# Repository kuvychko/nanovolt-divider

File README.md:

# nanovolt-divider

A programmable precision attenuator for nanovolt-to-microvolt experiments: it divides an ordinary
bench power supply down by **passive resistive division**, read by an external precision DMM. Three
ratios (1e-5, 1e-6, 1e-7), relay-controlled polarity reversal for ABBA modulation, and a
source-disconnected baseline that opens the source without touching the measurement path.
Measured end to end down to 1.4 nV (see [Status](#status)).

| | |
|---|---|
|  |  |
| INJECTING: K5 set, the source drives the 1E-6 divider | ISOLATED: the source is open at both ends, the 1 Ω and OUT jacks stay connected |

| | |
|---|---|
| Ranges | `1E-5`, `1E-6`, `1E-7`: high legs of 100 kΩ (0.1 %, 5 ppm/°C), 1 MΩ (0.1 %, 10 ppm/°C) and 10 MΩ (1 %) over one shared 1 Ω low leg |
| Polarity | K4 reverses the source *upstream* of the high leg, so relay-contact EMFs reach the output divided by ~1/k |
| Baseline | ISOLATE opens the source at both ends; the 1 Ω, its Kelvin taps and the DMM path are never switched |
| Switching | Five latching relays, pulsed for 20 ms and never held: no continuous coil power |
| Temperature | TMP275 on a slotted island next to the 1 Ω: monitoring, and a check that the instrument is used inside its calibrated span |
| Calibration | A calibrated ratio k0 per range with its uncertainty and validated temperature span, stored in NVS and backed up to microSD. The firmware also supports a temperature correction k(T) = k0 [1 + α(T−T0) + β(T−T0)²]; this unit's records carry none ([why](docs/calibration.md#temperature-monitored-not-corrected)) |
| Control | SCPI over USB serial, and a 2.8" touchscreen (ESP32 "Cheap Yellow Display") |

## Status

Rev A is built and verified: all relay transitions work, and with 10 V applied all three ratios read
within 0.25 % of nominal, with the ISOLATE reading unchanged by the source. Firmware is 0.2.2.

**Calibration: complete.** The three ratios are measured (1E-5 to ±37 ppm over 21–27 °C, plus the DMM's
range-to-range accuracy), and an end-to-end test recovered every injected signal from 1 µV down to
**1.39 ± 0.24 nV** at its predicted level, with the switching null at −0.03 ± 0.24 nV. The records
were written to the instrument on 2026-10-16 and read back identical. The method, every result and
the stored records are in [docs/calibration.md](docs/calibration.md).

## Documentation

| Document | Contents |
|---|---|
| [docs/nanovolt_divider_rev_a.md](docs/nanovolt_divider_rev_a.md) | Design: architecture, relay rules, control, calibration model, BOM |
| [docs/hardware.md](docs/hardware.md) | Circuit, relay states, display harness wiring, board layout and routing rules |
| [docs/development.md](docs/development.md) | Opening the KiCad project, the ERC/DRC baseline, the generators and router, fabrication files |
| [docs/host_interface.md](docs/host_interface.md) | Driving it from a computer: the USB link, the reset-on-open trap, the SCPI contract |
| [docs/calibration.md](docs/calibration.md) | How the ratios are calibrated, the uncertainty budget, and the results so far |
| [firmware/README.md](firmware/README.md) | Building and flashing, the full SCPI command reference, first power-on |

## Repository layout

```
docs/                      design, hardware, development, host interface, calibration
calibration/               calibration result data (summaries and figures)
enclosure/                 SOLIDWORKS parts (.SLDPRT), STEP, and 3D-print files (.3MF, .3DXML)
firmware/                  ESP32 firmware, PlatformIO: relay state machine, SCPI over USB, touch UI,
                           microSD calibration backup and run log
hardware/                  KiCad 10 project
  nanovolt-divider.kicad_pro
  nanovolt-divider.kicad_sch   root sheet: metrology topology (input, relays, high legs, 1 ohm, output)
  control.kicad_sch            ESP32 display-module harness, MCP23017, TMP275, power
  relay_channel.kicad_sch      generic latching-relay channel, instantiated 5x (K1..K5)
  nanovolt-divider.kicad_pcb   board: 60 x 69.1 mm, 2 layers
  nanovolt-divider.kicad_dru   custom DRC rules (1 ohm bridge track width)
  lib/                         project symbol and footprint libraries
  fab/                         Rev A Gerbers and drill files
tools/gen_schematics.py    generates the schematics and the project libraries
tools/gen_pcb.py           generates the placed, unrouted board
tools/route_pcb.py         grid maze router around the hand routes (see docs/hardware.md)
tools/route_hand.py        the hand routes and routing policy: the design intent of the routing
tools/pcb_io.py            pcbnew side of the router: dump pads, apply routes
tools/scpi.py              SCPI terminal for the instrument over USB serial (uv run tools/scpi.py)
```

## Building one

1. **Boards.** Zip the contents of `hardware/fab/` and order (they went to OSH Park). Everything is
   hand-solderable; the BOM is in [§11 of the design doc](docs/nanovolt_divider_rev_a.md#11-bom).
2. **Harness.** Wire the display module to `J7` / `J8` **by signal name, never by pad number**: the
   board silk does not match the module. The table is in
   [docs/hardware.md, Display harness](docs/hardware.md#display-harness).
3. **Enclosure.** Print and assemble it as below.
4. **Firmware.** Build, flash and power on following [firmware/README.md](firmware/README.md).

## Enclosure

The enclosure is 3D-printed. `enclosure/` has the SOLIDWORKS source (`.SLDPRT`), a neutral `.STEP`
and a print-ready `.3MF` for each part: front panel (it also serves as the display bezel), back
panel, base plate (v1), cover (v1), PCB holder, and a wrench for the banana-jack nuts. The version
is in each file name.

Every part prints in PLA on a Prusa i3 MK3S with a 0.4 mm nozzle, using PrusaSlicer's
**0.20 mm QUALITY** preset, 15 % infill, and **no supports**.

Before assembling, heat-set the knurled brass inserts: the M2 ones go into the PCB holder, the M3
ones into the enclosure parts. Fasteners, banana jacks, the display module, and the cables are
listed in [BOM §11.4 and §11.5](docs/nanovolt_divider_rev_a.md#114-front-panel--mechanical).

| | |
|---|---|
|  |  |
| Cover off: the board on its holder, the display behind the front panel, and the jacks wired to their pads | Base plate with printed feet, and the back panel with the USB opening |

## Known limitations

* The board's harness silk and F.Fab text describe a different module pinout from the module the
  instrument uses. Wire by signal name (see
  [Display harness](docs/hardware.md#display-harness)).
* The harness cable has no strain relief at the board end; nothing on the board takes that load.

## Datasheets

Not redistributed here. Panasonic TQ relays: catalog ASCTB14E (`industry.panasonic.com`); Ohmite
MOX-700 and Slim-Mox; Vishay Dale RS/NS; Microchip MCP23017; TI TMP275.

## License

* Hardware (`hardware/`), enclosure (`enclosure/`) and documentation (`docs/`, `calibration/`):
  [CERN-OHL-P-2.0](LICENSE-CERN-OHL-P-2.0).
* Firmware (`firmware/`) and tools (`tools/`): [MIT](LICENSE-MIT).

Source location: <https://github.com/kuvychko/nanovolt-divider>. See [LICENSE](LICENSE).

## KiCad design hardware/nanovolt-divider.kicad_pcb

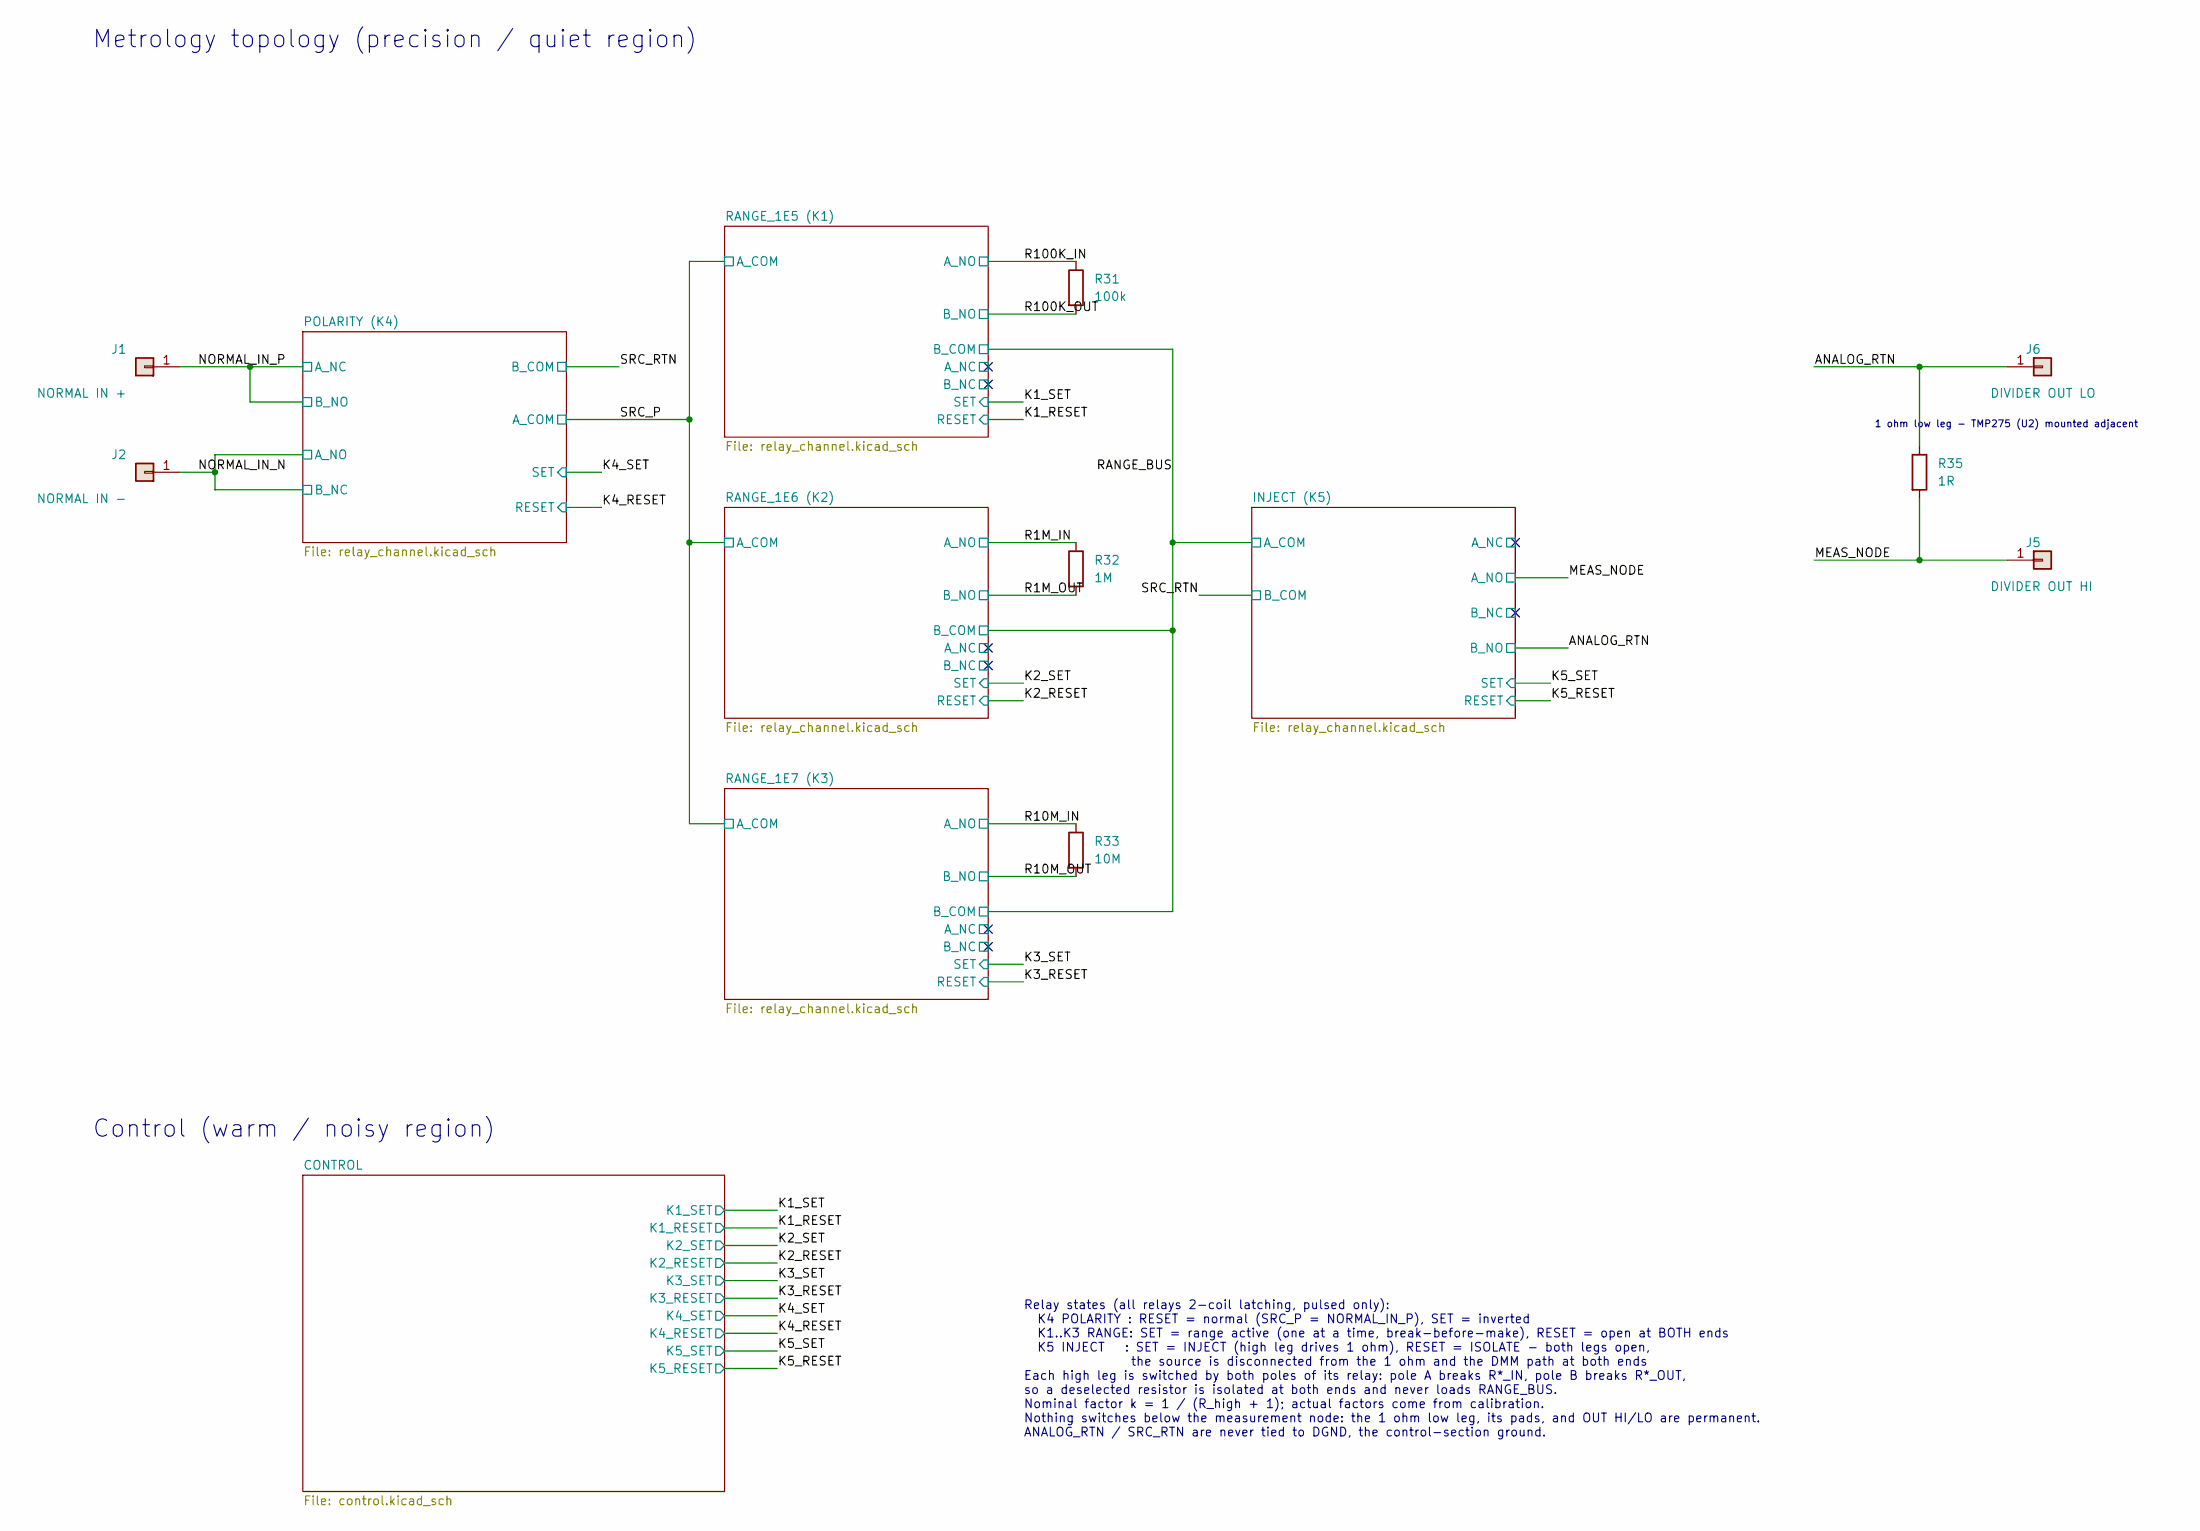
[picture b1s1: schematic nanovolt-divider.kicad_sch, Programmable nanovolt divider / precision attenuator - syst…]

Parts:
J1: NORMAL IN +; SolderWire-0.25sqmm_1x01_D0.65mm_OD1.7mm
J2: NORMAL IN -; SolderWire-0.25sqmm_1x01_D0.65mm_OD1.7mm
J5: DIVIDER OUT HI; SolderWire-0.25sqmm_1x01_D0.65mm_OD1.7mm
J6: DIVIDER OUT LO; SolderWire-0.25sqmm_1x01_D0.65mm_OD1.7mm
R31: 100k; R_Axial_Ohmite_MOX700_L7.0mm_D2.7mm_P10.16mm_Horizontal; MPN MOX70031003BZE
R32: 1M; R_Axial_Ohmite_MOX700_L7.0mm_D2.7mm_P10.16mm_Horizontal; MPN MOX70031004BYE
R33: 10M; R_Radial_Ohmite_SlimMox_SM102_L14.7mm_W2.5mm_P10.16mm; MPN SM102031005FE
R35: 1R; R_Axial_Vishay_RS02C_L15.1mm_D5.6mm_P20.32mm_Horizontal; MPN RS02C1R000FE70

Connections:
/ANALOG_RTN: J6.1, R35.1; also elsewhere on the board
/MEAS_NODE: J5.1, R35.2; also elsewhere on the board
/NORMAL_IN_N: J2.1; also elsewhere on the board
/NORMAL_IN_P: J1.1; also elsewhere on the board
/R1M_IN: R32.1; also elsewhere on the board
/R1M_OUT: R32.2; also elsewhere on the board
/R10M_IN: R33.1; also elsewhere on the board
/R10M_OUT: R33.2; also elsewhere on the board
/R100K_IN: R31.1; also elsewhere on the board
/R100K_OUT: R31.2; also elsewhere on the board

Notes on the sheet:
Metrology topology (precision / quiet region)
Control (warm / noisy region)
Relay states (all relays 2-coil latching, pulsed only): K4 POLARITY : RESET = normal (SRC_P = NORMAL_IN_P), SET = inverted K1..K3 RANGE: SET = range active (one at a time, break-before-make), RESET = open at BOTH ends K5 INJECT : SET = INJECT (high leg drives 1 ohm), RESET = ISOLATE - both legs ope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
1 ohm low leg - TMP275 (U2) mounted adjacent

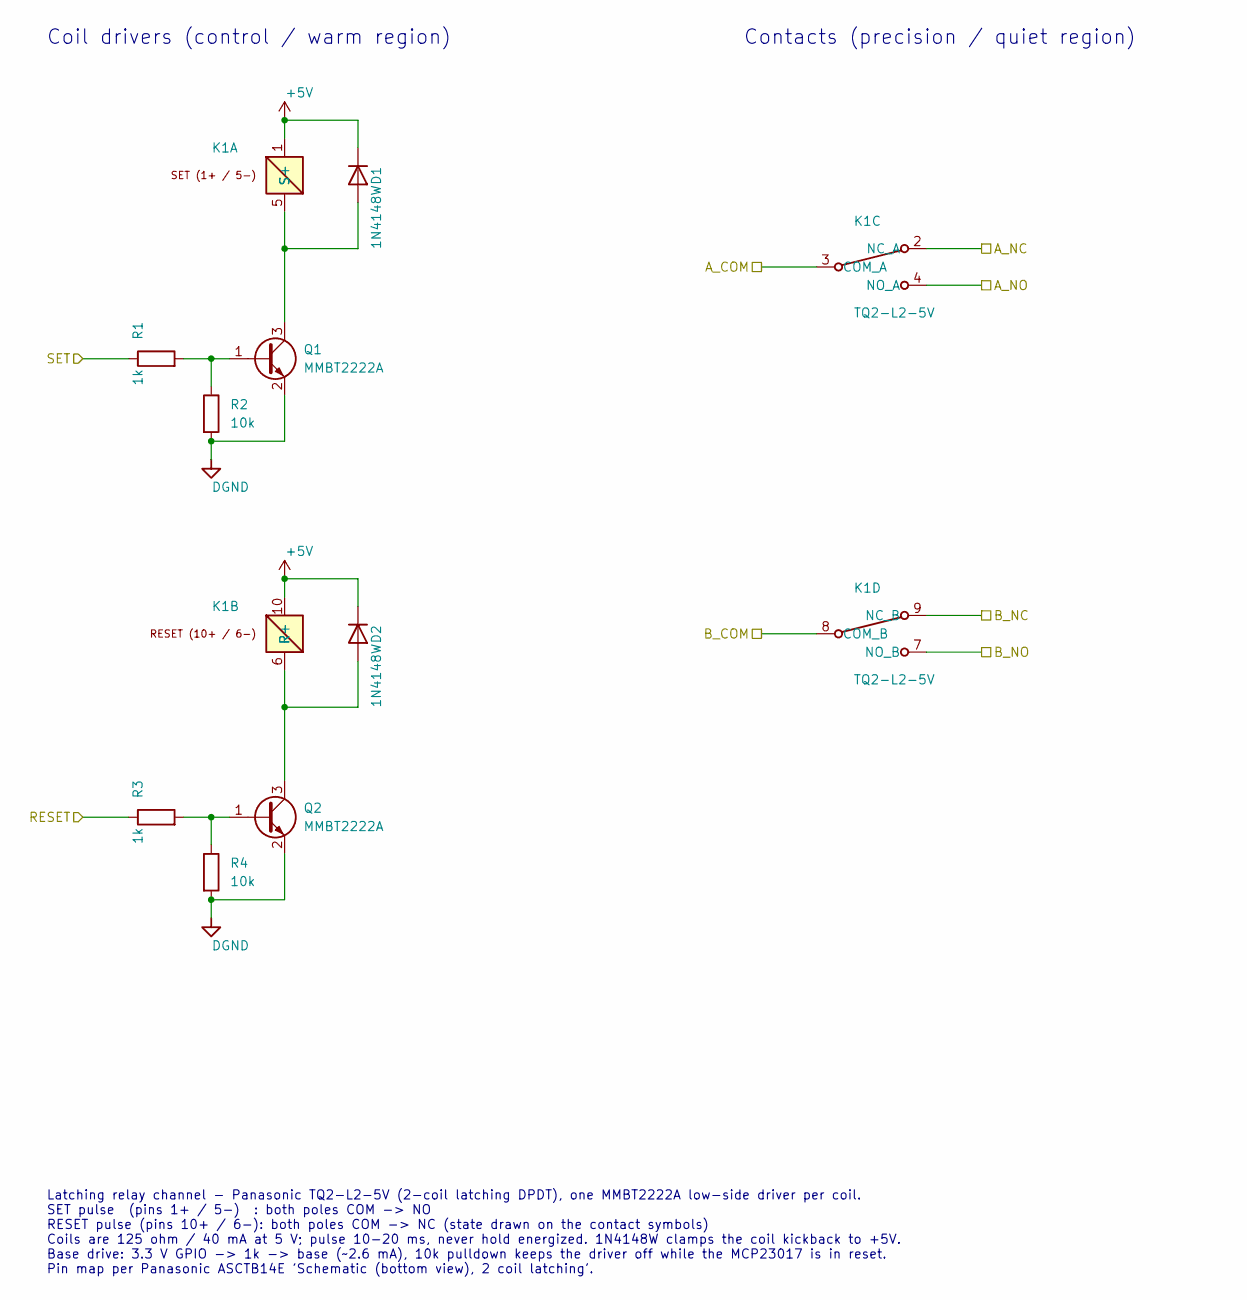
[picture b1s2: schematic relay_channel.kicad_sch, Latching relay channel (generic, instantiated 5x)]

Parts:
D1, D2: 1N4148W; D_SOD-123
K1: TQ2-L2-5V; Relay_DPDT_Panasonic_TQ2_THT
Q1, Q2: MMBT2222A; SOT-23
R1, R3: 1k; R_1206_3216Metric
R2, R4: 10k; R_1206_3216Metric

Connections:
+5V: D1.1 (K), D2.1 (K), K1.1 (S+), K1.10 (R+); also elsewhere on the board
/K1_RESET: R3.1; also elsewhere on the board
/K1_SET: R1.1; also elsewhere on the board
/R100K_IN: K1.4 (NO_A); also elsewhere on the board
/R100K_OUT: K1.7 (NO_B); also elsewhere on the board
/RANGE_1E5 (K1)/A_NC: K1.2 (NC_A)
/RANGE_1E5 (K1)/B_NC: K1.9 (NC_B)
/RANGE_BUS: K1.8 (COM_B); also elsewhere on the board
/SRC_P: K1.3 (COM_A); also elsewhere on the board
DGND: Q1.2 (E), Q2.2 (E), R2.2, R4.2; also elsewhere on the board
unnamed: D1.2 (A), K1.5 (S-), Q1.3 (C)
unnamed: D2.2 (A), K1.6 (R-), Q2.3 (C)
unnamed: Q1.1 (B), R1.2, R2.1
unnamed: Q2.1 (B), R3.2, R4.1

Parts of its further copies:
D3, D4, D5, D6, D7, D8, D9, D10: 1N4148W; D_SOD-123
K2, K3, K4, K5: TQ2-L2-5V; Relay_DPDT_Panasonic_TQ2_THT
Q3, Q4, Q5, Q6, Q7, Q8, Q9, Q10: MMBT2222A; SOT-23
R5, R7, R9, R11, R13, R15, R17, R19: 1k; R_1206_3216Metric
R6, R8, R10, R12, R14, R16, R18, R20: 10k; R_1206_3216Metric

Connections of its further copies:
+5V: D3.1 (K), D4.1 (K), D5.1 (K), D6.1 (K), D7.1 (K), D8.1 (K), D9.1 (K), D10.1 (K), K2.1 (S+), K2.10 (R+), K3.1 (S+), K3.10 (R+), K4.1 (S+), K4.10 (R+), K5.1 (S+), K5.10 (R+); also elsewhere on the board
/ANALOG_RTN: K5.7 (NO_B); also elsewhere on the board
/INJECT (K5)/A_NC: K5.2 (NC_A)
/INJECT (K5)/B_NC: K5.9 (NC_B)
/K2_RESET: R7.1; also elsewhere on the board
/K2_SET: R5.1; also elsewhere on the board
/K3_RESET: R11.1; also elsewhere on the board
/K3_SET: R9.1; also elsewhere on the board
/K4_RESET: R15.1; also elsewhere on the board
/K4_SET: R13.1; also elsewhere on the board
/K5_RESET: R19.1; also elsewhere on the board
/K5_SET: R17.1; also elsewhere on the board
/MEAS_NODE: K5.4 (NO_A); also elsewhere on the board
/NORMAL_IN_N: K4.4 (NO_A), K4.9 (NC_B); also elsewhere on the board
/NORMAL_IN_P: K4.2 (NC_A), K4.7 (NO_B); also elsewhere on the board
/R1M_IN: K2.4 (NO_A); also elsewhere on the board
/R1M_OUT: K2.7 (NO_B); also elsewhere on the board
/R10M_IN: K3.4 (NO_A); also elsewhere on the board
/R10M_OUT: K3.7 (NO_B); also elsewhere on the board
/RANGE_1E6 (K2)/A_NC: K2.2 (NC_A)
/RANGE_1E6 (K2)/B_NC: K2.9 (NC_B)
/RANGE_1E7 (K3)/A_NC: K3.2 (NC_A)
/RANGE_1E7 (K3)/B_NC: K3.9 (NC_B)
/RANGE_BUS: K2.8 (COM_B), K3.8 (COM_B), K5.3 (COM_A); also elsewhere on the board
/SRC_P: K2.3 (COM_A), K3.3 (COM_A), K4.3 (COM_A); also elsewhere on the board
/SRC_RTN: K4.8 (COM_B), K5.8 (COM_B)
DGND: Q3.2 (E), Q4.2 (E), Q5.2 (E), Q6.2 (E), Q7.2 (E), Q8.2 (E), Q9.2 (E), Q10.2 (E), R6.2, R8.2, R10.2, R12.2, R14.2, R16.2, R18.2, R20.2; also elsewhere on the board
unnamed: D3.2 (A), K2.5 (S-), Q3.3 (C)
unnamed: D4.2 (A), K2.6 (R-), Q4.3 (C)
unnamed: D5.2 (A), K3.5 (S-), Q5.3 (C)
unnamed: D6.2 (A), K3.6 (R-), Q6.3 (C)
unnamed: D7.2 (A), K4.5 (S-), Q7.3 (C)
unnamed: D8.2 (A), K4.6 (R-), Q8.3 (C)
unnamed: D9.2 (A), K5.5 (S-), Q9.3 (C)
unnamed: D10.2 (A), K5.6 (R-), Q10.3 (C)
unnamed: Q3.1 (B), R5.2, R6.1
unnamed: Q4.1 (B), R7.2, R8.1
unnamed: Q5.1 (B), R9.2, R10.1
unnamed: Q6.1 (B), R11.2, R12.1
unnamed: Q7.1 (B), R13.2, R14.1
unnamed: Q8.1 (B), R15.2, R16.1
unnamed: Q9.1 (B), R17.2, R18.1
unnamed: Q10.1 (B), R19.2, R20.1

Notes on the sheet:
Latching relay channel - Panasonic TQ2-L2-5V (2-coil latching DPDT), one MMBT2222A low-side driver per coil. SET pulse (pins 1+ / 5-) : both poles COM -> NO RESET pulse (pins 10+ / 6-): both poles COM -> NC (state drawn on the contact symbols) Coils are 125 ohm / 40 mA at 5 V; pulse 10-20 ms, never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
Coil drivers (control / warm region)
Contacts (precision / quiet region)

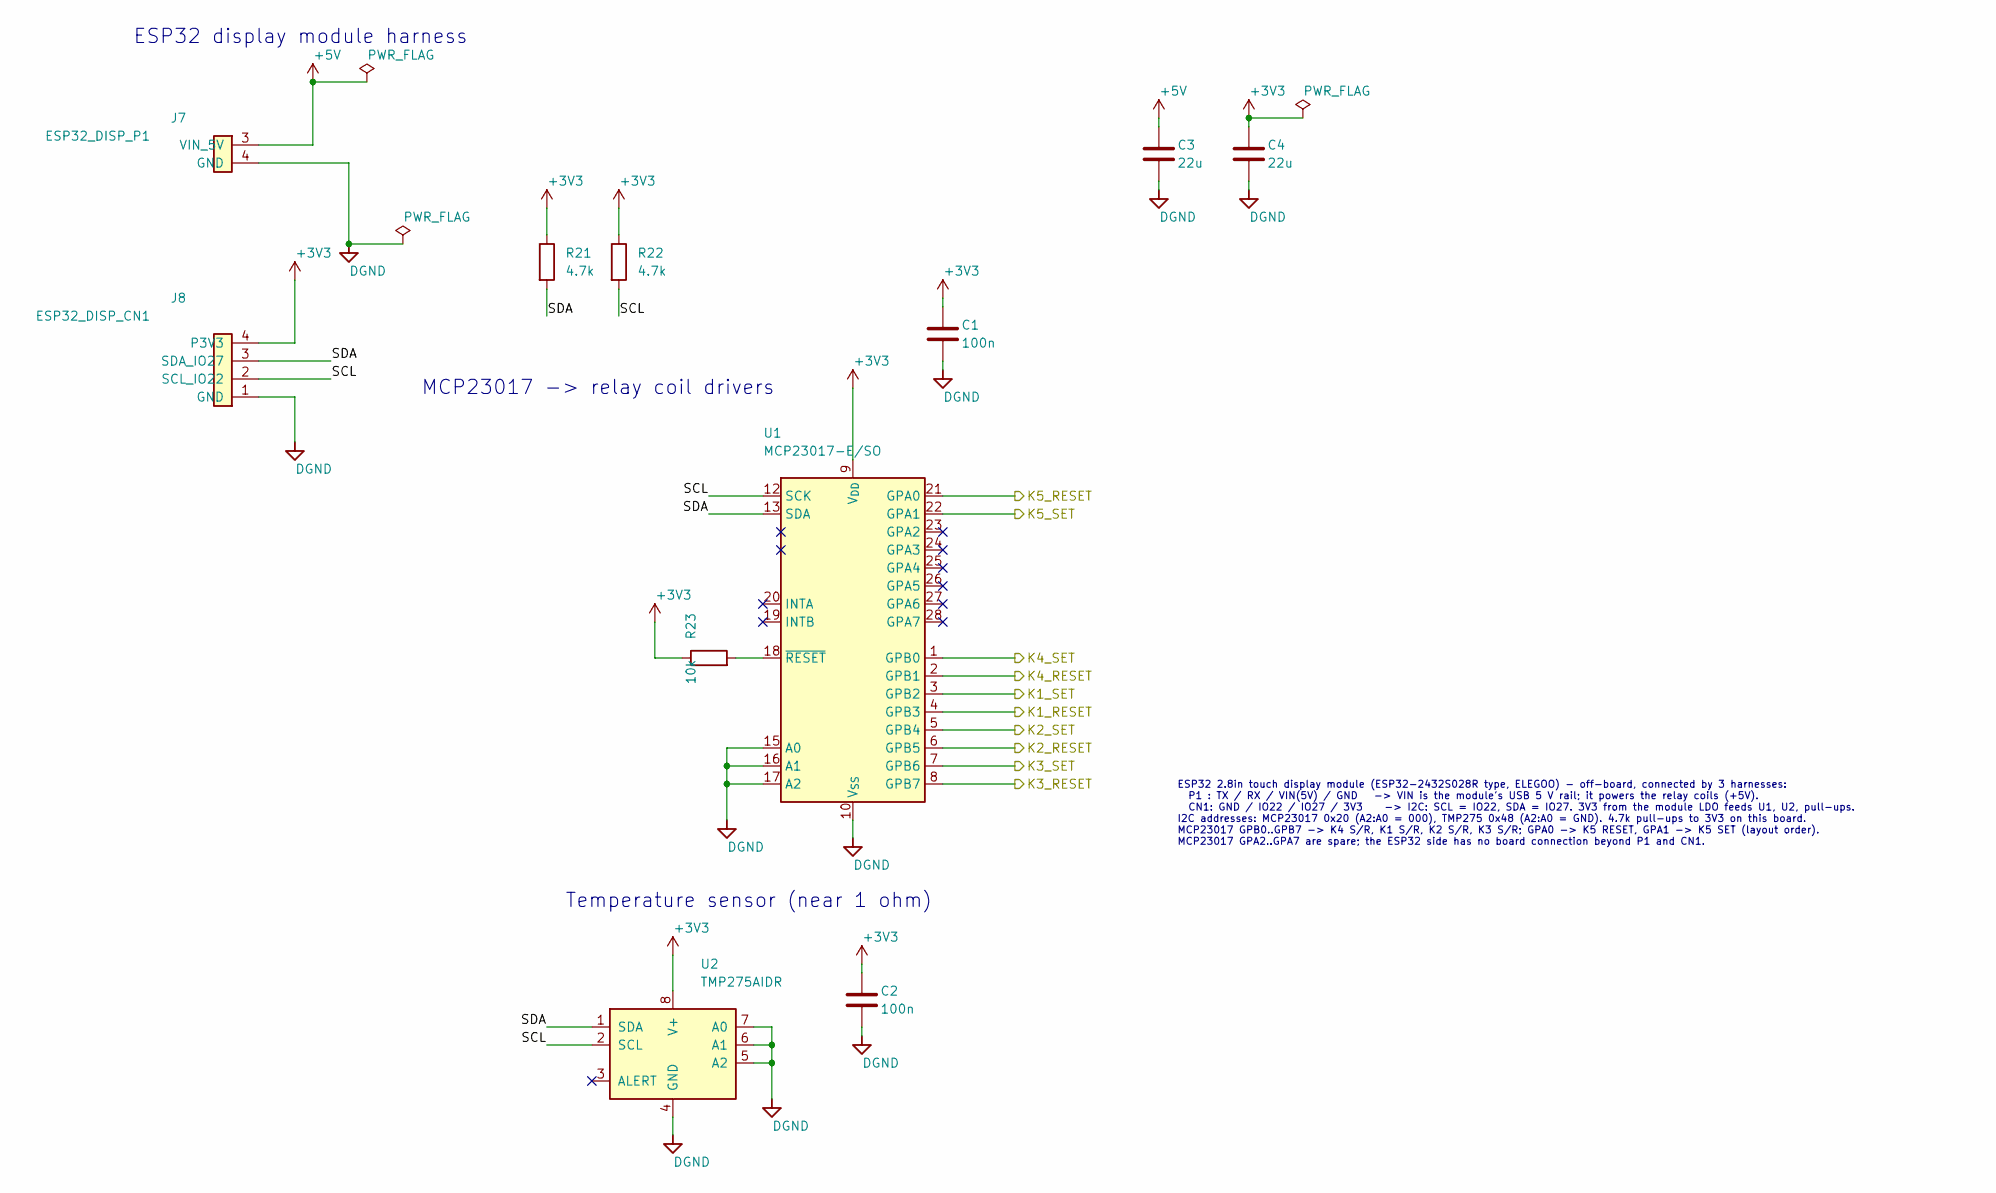
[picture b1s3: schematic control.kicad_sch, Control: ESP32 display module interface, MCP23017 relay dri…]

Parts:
C1, C2: 100n; C_1206_3216Metric; MPN SH31B104K160CT
C3, C4: 22u; C_1206_3216Metric; MPN EMK316BB7226ML-T
J7: ESP32_DISP_P1; J_ESP32_P1_WirePads
J8: ESP32_DISP_CN1; J_ESP32_CN1_WirePads
R21, R22: 4.7k; R_1206_3216Metric
R23: 10k; R_1206_3216Metric
U1: MCP23017-E/SO; SOIC-28W_7.5x17.9mm_P1.27mm; MPN MCP23017-E/SO
U2: TMP275AIDR; SOIC-8_3.9x4.9mm_P1.27mm; MPN TMP275AIDR

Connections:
+3V3: C1.1, C2.1, C4.1, J8.4 (P3V3), R21.1, R22.1, R23.1, U1.9 (V_{DD}), U2.8 (V+)
+5V: C3.1, J7.3 (VIN_5V); also elsewhere on the board
/CONTROL/SCL: J8.2 (SCL_IO22), R22.2, U1.12 (SCK), U2.2 (SCL)
/CONTROL/SDA: J8.3 (SDA_IO27), R21.2, U1.13 (SDA), U2.1 (SDA)
/K1_RESET: U1.4 (GPB3); also elsewhere on the board
/K1_SET: U1.3 (GPB2); also elsewhere on the board
/K2_RESET: U1.6 (GPB5); also elsewhere on the board
/K2_SET: U1.5 (GPB4); also elsewhere on the board
/K3_RESET: U1.8 (GPB7); also elsewhere on the board
/K3_SET: U1.7 (GPB6); also elsewhere on the board
/K4_RESET: U1.2 (GPB1); also elsewhere on the board
/K4_SET: U1.1 (GPB0); also elsewhere on the board
/K5_RESET: U1.21 (GPA0); also elsewhere on the board
/K5_SET: U1.22 (GPA1); also elsewhere on the board
DGND: C1.2, C2.2, C3.2, C4.2, J7.4 (GND), J8.1 (GND), U1.10 (V_{SS}), U1.15 (A0), U1.16 (A1), U1.17 (A2), U2.4 (GND), U2.5 (A2), U2.6 (A1), U2.7 (A0); also elsewhere on the board
unnamed: R23.2, U1.18 (~RESET)

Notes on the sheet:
ESP32 2.8in touch display module (ESP32-2432S028R type, ELEGOO) - off-board, connected by 3 harnesses: P1 : TX / RX / VIN(5V) / GND -> VIN is the module's USB 5 V rail; it powers the relay coils (+5V). CN1: GND / IO22 / IO27 / 3V3 -> I2C: SCL = IO22, SDA = IO27. 3V3 from the module LDO feeds U1, U2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
ESP32 display module harness
MCP23017 -> relay coil drivers
Temperature sensor (near 1 ohm)

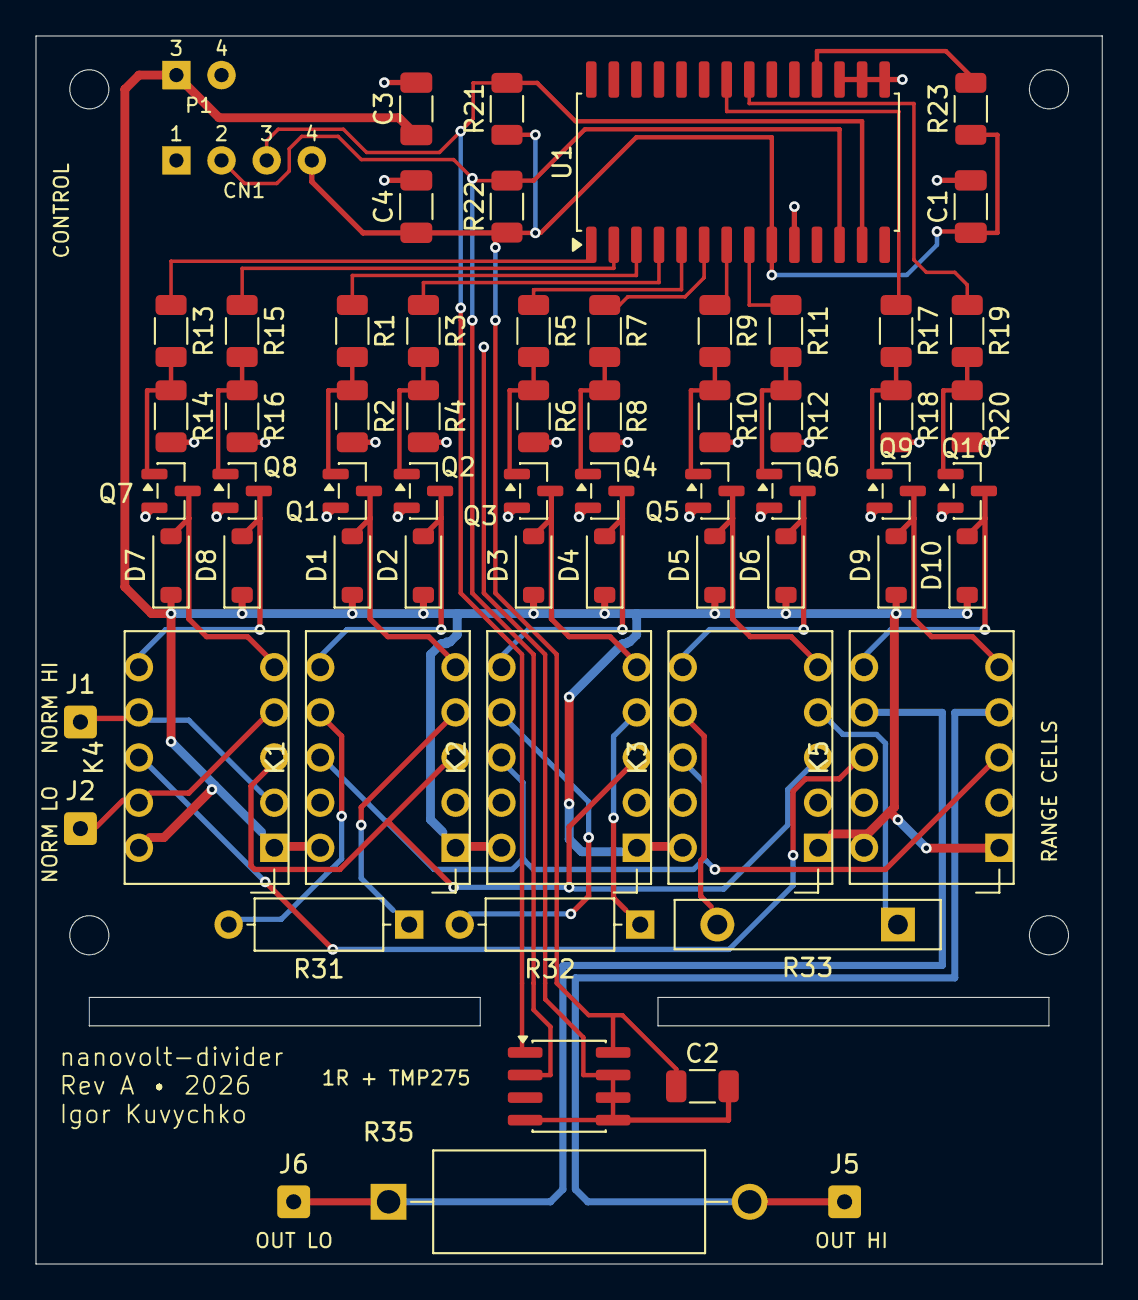
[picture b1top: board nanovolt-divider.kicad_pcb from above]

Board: 2 copper layers, 60.0 x 69.1 mm, 68 parts (0 on the bottom side), 49 nets.

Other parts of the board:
H1, H2, H3, H4: M2; MountingHole_2.2mm_M2

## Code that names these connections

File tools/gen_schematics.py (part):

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    # GPB0..GPB7 (pins 1-8) are the package row that faces the driver columns, so they take eight
    # lines in the columns' own left-to-right order and fan out without crossing.  K5's two lines are
    # on GPA0/GPA1 and leave under the package to the right; GPA0 is the outer of the two there, so
    # it takes K5_RESET, whose driver is the outer column.  Firmware maps GPIO -> coil by table.
    # (GPA7/GPB7 are output-only on current MCP23017 silicon; every pin here is an output.)
    gp = [("1", "K4_SET"), ("2", "K4_RESET"), ("3", "K1_SET"), ("4", "K1_RESET"), ("5", "K2_SET"),
          ("6", "K2_RESET"), ("7", "K3_SET"), ("8", "K3_RESET"), ("21", "K5_RESET"), ("22", "K5_SET")]
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             page="6")
    # NIN+ -> A_NC and B_NO ; NIN- -> A_NO and B_NC
    sh.wire(nin_p[0], nin_p[1], px, 60.96)
    sh.label("NORMAL_IN_P", 40.64, 60.96)
    sh.junction(48.26, 60.96)
    sh.poly((48.26, 60.96), (48.26, 66.04), (px, 66.04))
    sh.wire(nin_n[0], nin_n[1], 43.18, 76.2)
    sh.label("NORMAL_IN_N", 40.64, 76.2)
    sh.junction(43.18, 76.2)
    sh.poly((43.18, 76.2), (43.18, 73.66), (px, 73.66))
    sh.poly((43.18, 76.2), (43.18, 78.74), (px, 78.74))
    # K4 control
    sh.wire(px + 38.1, 76.2, 99.06, 76.2)
    sh.label("K4_SET", 99.06, 76.2)
    sh.wire(px + 38.1, 81.28, 99.06, 81.28)
    sh.label("K4_RESET", 99.06, 81.28)
    # SRC+ (A_COM) -> range relay bus ; SRC- (B_COM) -> 3PDT pole 2 NORMAL
    src_p = (px + 38.1, 68.58)
    src_n = (px + 38.1, 60.96)
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        sh.label(f"{kref}_RESET", 160.02, y + 27.94)
    # SRC+ bus
    sh.wire(src_p[0], src_p[1], bus_x, src_p[1])
    sh.label("SRC_P", 101.6, src_p[1])
    ys = sorted(set(a_com_ys + [src_p[1]]))
    for a, b in zip(ys, ys[1:]):
        sh.wire(bus_x, a, bus_x, b)
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    for yy in ys[1:-1]:
        sh.junction(rbus_x, yy)
    sh.wire(rbus_x, inj_in[1], inj_in[0], inj_in[1])
    sh.label("RANGE_BUS", rbus_x, 76.2, 180)

    # ---- INJECT / ISOLATE relay -------------------------------------------------------------------
    sh.sheet("INJECT (K5)", RC, RELAY_UUIDS[4], ix, iy, 38.1, 30.48,
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    # Pole B breaks the return leg in step with pole A, so ISOLATE disconnects the programmable
    # source from the measurement node at BOTH ends: SRC_RTN -> B_COM, B_NO -> ANALOG_RTN.
    sh.wire(185.42, iy + 12.7, ix, iy + 12.7)
    sh.label("SRC_RTN", 185.42, iy + 12.7, 180)
    sh.wire(ix + 38.1, iy + 20.32, 238.76, iy + 20.32)
    sh.label("ANALOG_RTN", 238.76, iy + 20.32)
    for off in (5.08, 15.24):
        sh.noconn(ix + 38.1, iy + off)
    sh.wire(ix + 38.1, iy + 25.4, 236.22, iy + 25.4)
    sh.label("K5_SET", 236.22, iy + 25.4)
    sh.wire(ix + 38.1, iy + 27.94, 236.22, iy + 27.94)
    sh.label("K5_RESET", 236.22, iy + 27.94)
    inj_node = (ix + 38.1, iy + 10.16)

    # K4 pole B common is the source return: K4 B_COM -> SRC_RTN -> K5 B_COM.  Carried by name
    # rather than a polyline, which would have to cross the whole range-relay column.
    sh.wire(src_n[0], src_n[1], 101.6, src_n[1])
    sh.label("SRC_RTN", 101.6, src_n[1])

    # A_NO is the measurement node itself.  There is no source selector any more: the HV divider
    # was removed with Rev A (its ratio was capped by the shared 1 ohm low leg, and any value light
    # enough not to drag down a Geiger supply left too little signal), so nothing switches here.
    sh.wire(inj_node[0], inj_node[1], 238.76, inj_node[1])
    sh.label("MEAS_NODE", 238.76, inj_node[1])

    # ---- measurement node, 1 ohm low leg, output ---------------------------------------------------
    rlx = 289.56
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    out_lo = jack(307.34, 60.96, "J6", "DIVIDER OUT LO", 0, "Front panel banana jack, divider output LO (to DMM LO)")
    hi_y, lo_y = out_hi[1], out_lo[1]
    sh.wire(274.32, hi_y, rlx, hi_y)
    sh.label("MEAS_NODE", 274.32, hi_y)
    sh.junction(rlx, hi_y)
    sh.wire(rlx, hi_y, rl_bot[0], rl_bot[1])
    sh.wire(rlx, hi_y, out_hi[0], out_hi[1])
    sh.wire(274.32, lo_y, rlx, lo_y)
    sh.label("ANALOG_RTN", 274.32, lo_y)
    sh.junction(rlx, lo_y)
    sh.wire(rlx, lo_y, rl_top[0], rl_top[1])
    sh.wire(rlx, lo_y, out_lo[0], out_lo[1])
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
